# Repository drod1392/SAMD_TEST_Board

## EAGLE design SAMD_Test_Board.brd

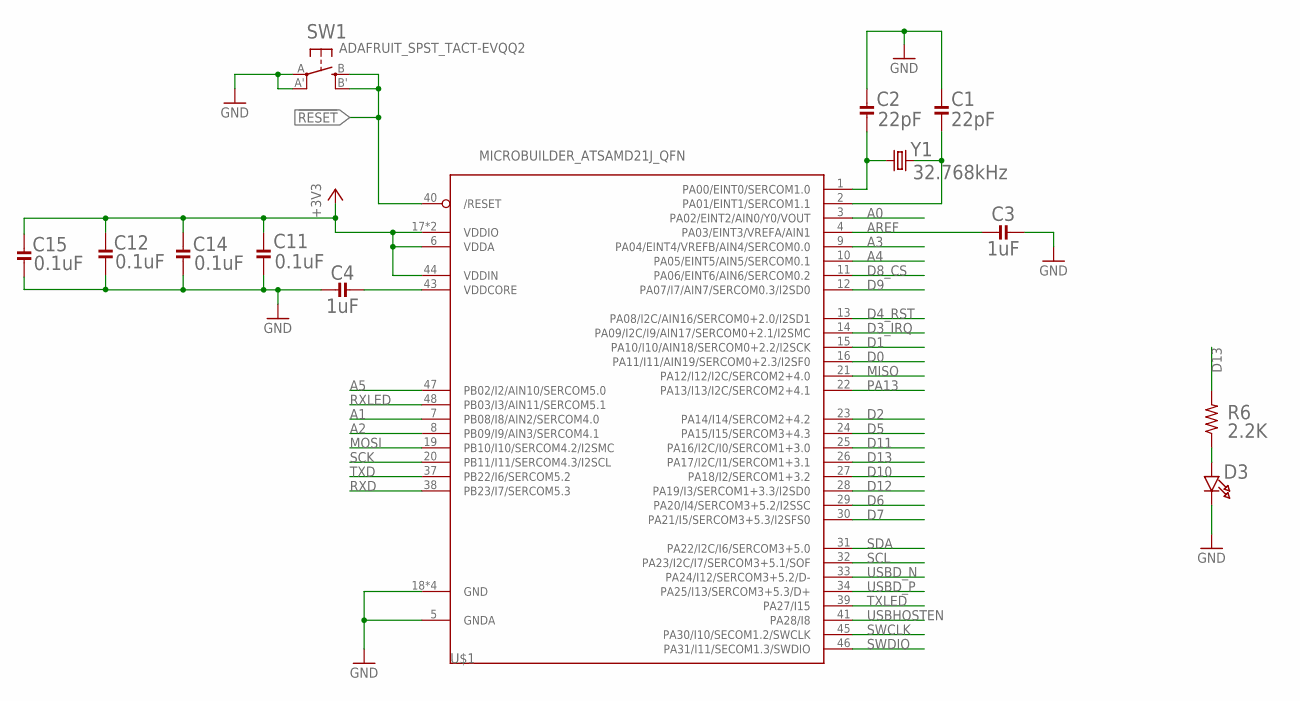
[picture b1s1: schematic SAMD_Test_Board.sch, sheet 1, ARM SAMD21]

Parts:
C1, C2: 22pF; MICROBUILDER__0805
C3, C4: 1uF; MICROBUILDER__0805
C11, C12, C14, C15: 0.1uF; MICROBUILDER__0805
D3: MICROBUILDER_LED0603; MICROBUILDER_CHIPLED_0603
R6: 2.2K; R0805
SW1: ADAFRUIT_SPST_TACT-EVQQ2; ADAFRUIT_EVQ-Q2
U$1: MICROBUILDER_ATSAMD21J_QFN; MICROBUILDER_TQFN48_7MM
Y1: 32.768kHz; CRYSTAL-SMD-3.2X1.5MM

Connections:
!RESET: SW1.B (S), SW1.B' (S1), U$1.40 (/RESET)
+3V3: C11.2, C12.2, C14.2, C15.2, U$1.6 (VDDA), U$1.17 (VDDIO), U$1.36 (VDDIO), U$1.44 (VDDIN); also elsewhere on the board
A0: U$1.3 (PA02/EINT2/AIN0/Y0/VOUT)
A1: U$1.7 (PB08/I8/AIN2/SERCOM4.0)
A2: U$1.8 (PB09/I9/AIN3/SERCOM4.1)
A3: U$1.9 (PA04/EINT4/VREFB/AIN4/SERCOM0.0)
A4: U$1.10 (PA05/EINT5/AIN5/SERCOM0.1)
A5: U$1.47 (PB02/I2/AIN10/SERCOM5.0)
AREF: C3.2, U$1.4 (PA03/EINT3/VREFA/AIN1)
D0: U$1.16 (PA11/I11/AIN19/SERCOM0+2.3/I2SF0); also elsewhere on the board
D1: U$1.15 (PA10/I10/AIN18/SERCOM0+2.2/I2SCK)
D2: U$1.23 (PA14/I14/SERCOM2+4.2)
D3_IRQ: U$1.14 (PA09/I2C/I9/AIN17/SERCOM0+2.1/I2SMC); also elsewhere on the board
D4_RST: U$1.13 (PA08/I2C/AIN16/SERCOM0+2.0/I2SD1); also elsewhere on the board
D5: U$1.24 (PA15/I15/SERCOM3+4.3)
D6: U$1.29 (PA20/I4/SERCOM3+5.2/I2SSC)
D7: U$1.30 (PA21/I5/SERCOM3+5.3/I2SFS0)
D8_CS: U$1.11 (PA06/EINT6/AIN6/SERCOM0.2); also elsewhere on the board
D9: U$1.12 (PA07/I7/AIN7/SERCOM0.3/I2SD0); also elsewhere on the board
D10: U$1.27 (PA18/I2/SERCOM1+3.2)
D11: U$1.25 (PA16/I2C/I0/SERCOM1+3.0); also elsewhere on the board
D12: U$1.28 (PA19/I3/SERCOM1+3.3/I2SD0)
D13: R6.2, U$1.26 (PA17/I2C/I1/SERCOM1+3.1)
GND: C1.2, C2.2, C3.1, C4.2, C11.1, C12.1, C14.1, C15.1, D3.C, SW1.A, SW1.A' (P1), U$1.5 (GNDA), U$1.18 (GND), U$1.35 (GND), U$1.42 (GND), U$1.THERMAL (GND); also elsewhere on the board
MISO: U$1.21 (PA12/I12/I2C/SERCOM2+4.0); also elsewhere on the board
MOSI: U$1.19 (PB10/I10/SERCOM4.2/I2SMC); also elsewhere on the board
unnamed: C2.1, U$1.1 (PA00/EINT0/SERCOM1.0), Y1.P$1 (1)
unnamed: C1.1, U$1.2 (PA01/EINT1/SERCOM1.1), Y1.P$2 (2)
unnamed: C4.1, U$1.43 (VDDCORE)
unnamed: D3.A, R6.1
PA13: U$1.22 (PA13/I13/I2C/SERCOM2+4.1)
RXD: U$1.38 (PB23/I7/SERCOM5.3)
RXLED: U$1.48 (PB03/I3/AIN11/SERCOM5.1)
SCK: U$1.20 (PB11/I11/SERCOM4.3/I2SCL); also elsewhere on the board
SCL: U$1.32 (PA23/I2C/I7/SERCOM3+5.1/SOF); also elsewhere on the board
SDA: U$1.31 (PA22/I2C/I6/SERCOM3+5.0); also elsewhere on the board
SWCLK: U$1.45 (PA30/I10/SECOM1.2/SWCLK); also elsewhere on the board
SWDIO: U$1.46 (PA31/I11/SECOM1.3/SWDIO); also elsewhere on the board
TXD: U$1.37 (PB22/I6/SERCOM5.2)
TXLED: U$1.39 (PA27/I15)
USBD_N: U$1.33 (PA24/I12/SERCOM3+5.2/D-); also elsewhere on the board
USBD_P: U$1.34 (PA25/I13/SERCOM3+5.3/D+); also elsewhere on the board
USBHOSTEN: U$1.41 (PA28/I8)

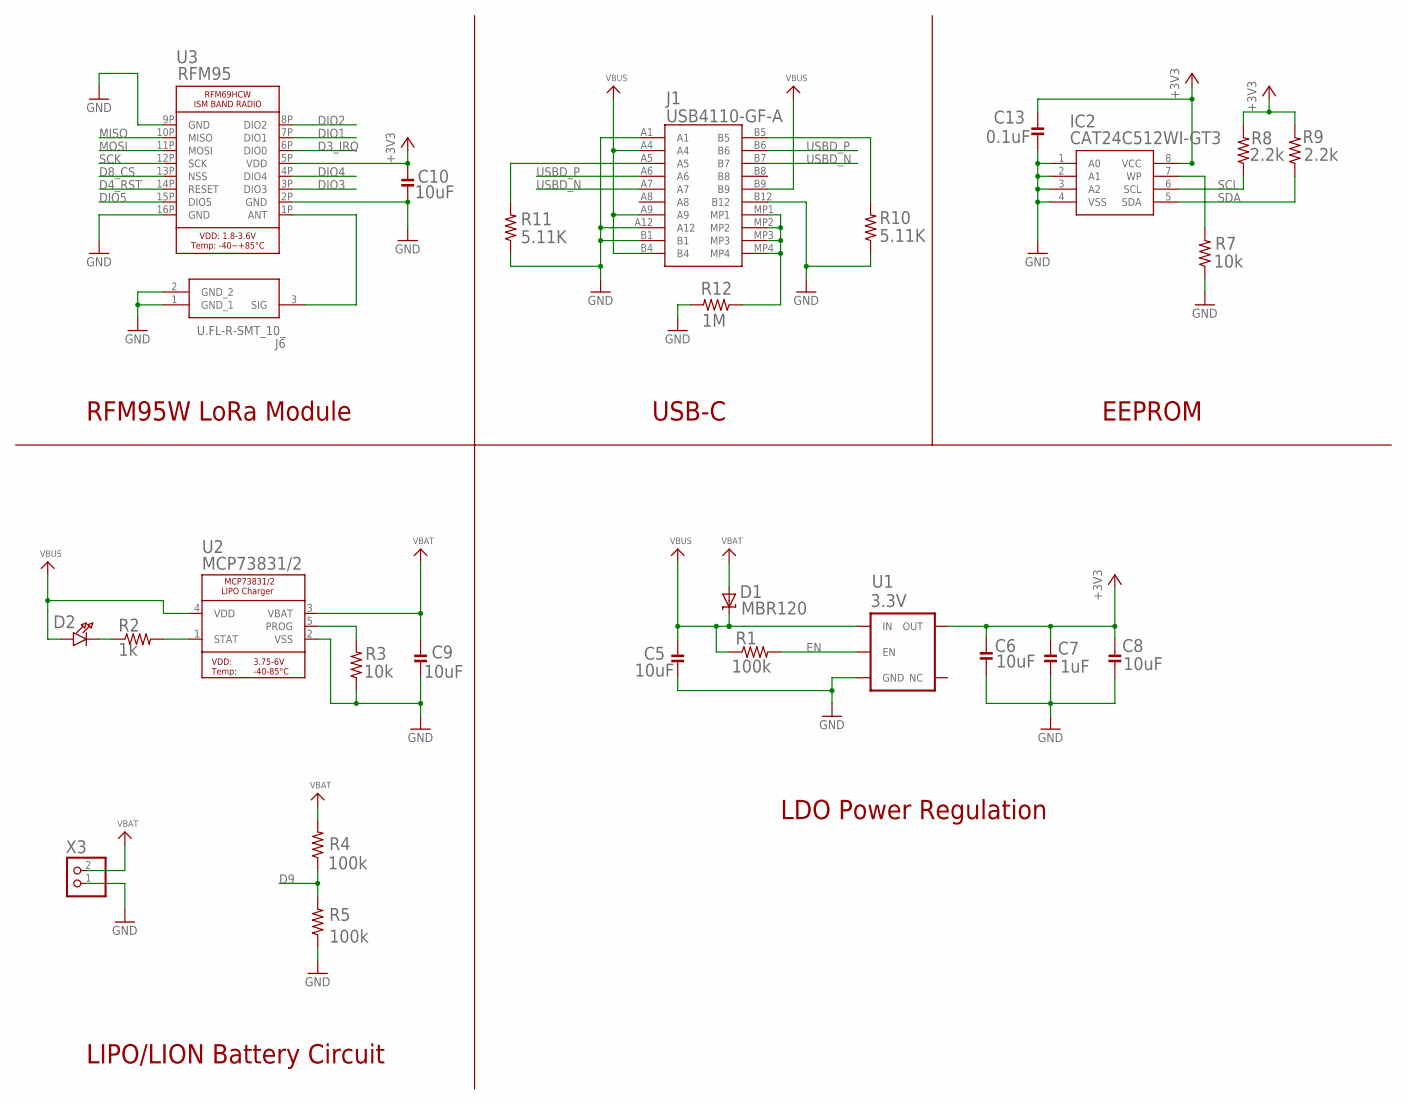
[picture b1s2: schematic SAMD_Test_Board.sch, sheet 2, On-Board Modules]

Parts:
C5, C6, C8, C9, C10: 10uF; MICROBUILDER__0805
C7: 1uF; MICROBUILDER__0805
C13: 0.1uF; MICROBUILDER__0805
D1: MBR120; MICROBUILDER_SOD-123
D2: MICROBUILDER_LED0603; MICROBUILDER_CHIPLED_0603
IC2: CAT24C512WI-GT3; SOIC127P600X175-8N
J1: USB4110-GF-A; USB4110GFA
J6: U.FL-R-SMT_10_; UFLRSMT10
R1, R4, R5: 100k; R0805
R2: 1k; R0805
R3, R7: 10k; R0805
R8: 2.2k; R0805; MOUSER CR0805-JW-202ELF
R9: 2.2k; R0805
R10, R11: 5.11K; R0805
R12: 1M; R0805
U1: 3.3V; SOT23-5
U2: MCP73831/2; MICROBUILDER_SOT23-5
U3: RFM95; MICROBUILDER_RFMHCW_SMT
X3: MICROBUILDER_CON_JST_PH_2PIN; MICROBUILDER_JSTPH2

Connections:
+3V3: C6.2, C7.2, C8.2, C10.2, C13.2, IC2.8 (VCC), R8.2, R9.2, U1.5 (OUT), U3.5P (VDD); also elsewhere on the board
D3_IRQ: U3.6P (DIO0); also elsewhere on the board
D4_RST: U3.14P (RESET); also elsewhere on the board
D8_CS: U3.13P (NSS); also elsewhere on the board
D9: R4.1, R5.2; also elsewhere on the board
DIO1: U3.7P (DIO1)
DIO2: U3.8P (DIO2)
DIO3: U3.3P (DIO3)
DIO4: U3.4P (DIO4)
DIO5: U3.15P (DIO5)
EN: R1.2, U1.3 (EN); also elsewhere on the board
GND: C5.1, C6.1, C7.1, C8.1, C9.1, C10.1, C13.1, IC2.1 (A0), IC2.2 (A1), IC2.3 (A2), IC2.4 (VSS), J1.A1, J1.A12, J1.B1, J1.B12, J6.1 (GND_1), J6.2 (GND_2), R3.1, R5.1, R7.1, R10.1, R11.1, R12.2, U1.2 (GND), U2.2 (VSS), U3.2P (GND), U3.9P (GND), U3.16P (GND), X3.1; also elsewhere on the board
MISO: U3.10P (MISO); also elsewhere on the board
MOSI: U3.11P (MOSI); also elsewhere on the board
unnamed: IC2.7 (WP), R7.2
unnamed: J1.A5, R11.2
unnamed: D2.C, R2.1
unnamed: R2.2, U2.1 (STAT)
unnamed: R3.2, U2.5 (PROG)
unnamed: J1.B5, R10.2
unnamed: J1.MP1, J1.MP2, J1.MP3, J1.MP4, R12.1
unnamed: J6.3 (SIG), U3.1P (ANT)
SCK: U3.12P (SCK); also elsewhere on the board
SCL: IC2.6 (SCL), R8.1; also elsewhere on the board
SDA: IC2.5 (SDA), R9.1; also elsewhere on the board
USBD_N: J1.A7, J1.B7; also elsewhere on the board
USBD_P: J1.A6, J1.B6; also elsewhere on the board
VBAT: C9.2, D1.A, R4.2, U2.3 (VBAT), X3.2
VBUS: C5.2, D1.C, D2.A, J1.A4, J1.A9, J1.B4, J1.B9, R1.1, U1.1 (IN), U2.4 (VDD)

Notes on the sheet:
LIPO/LION Battery Circuit
RFM95W LoRa Module
USB-C
EEPROM
LDO Power Regulation

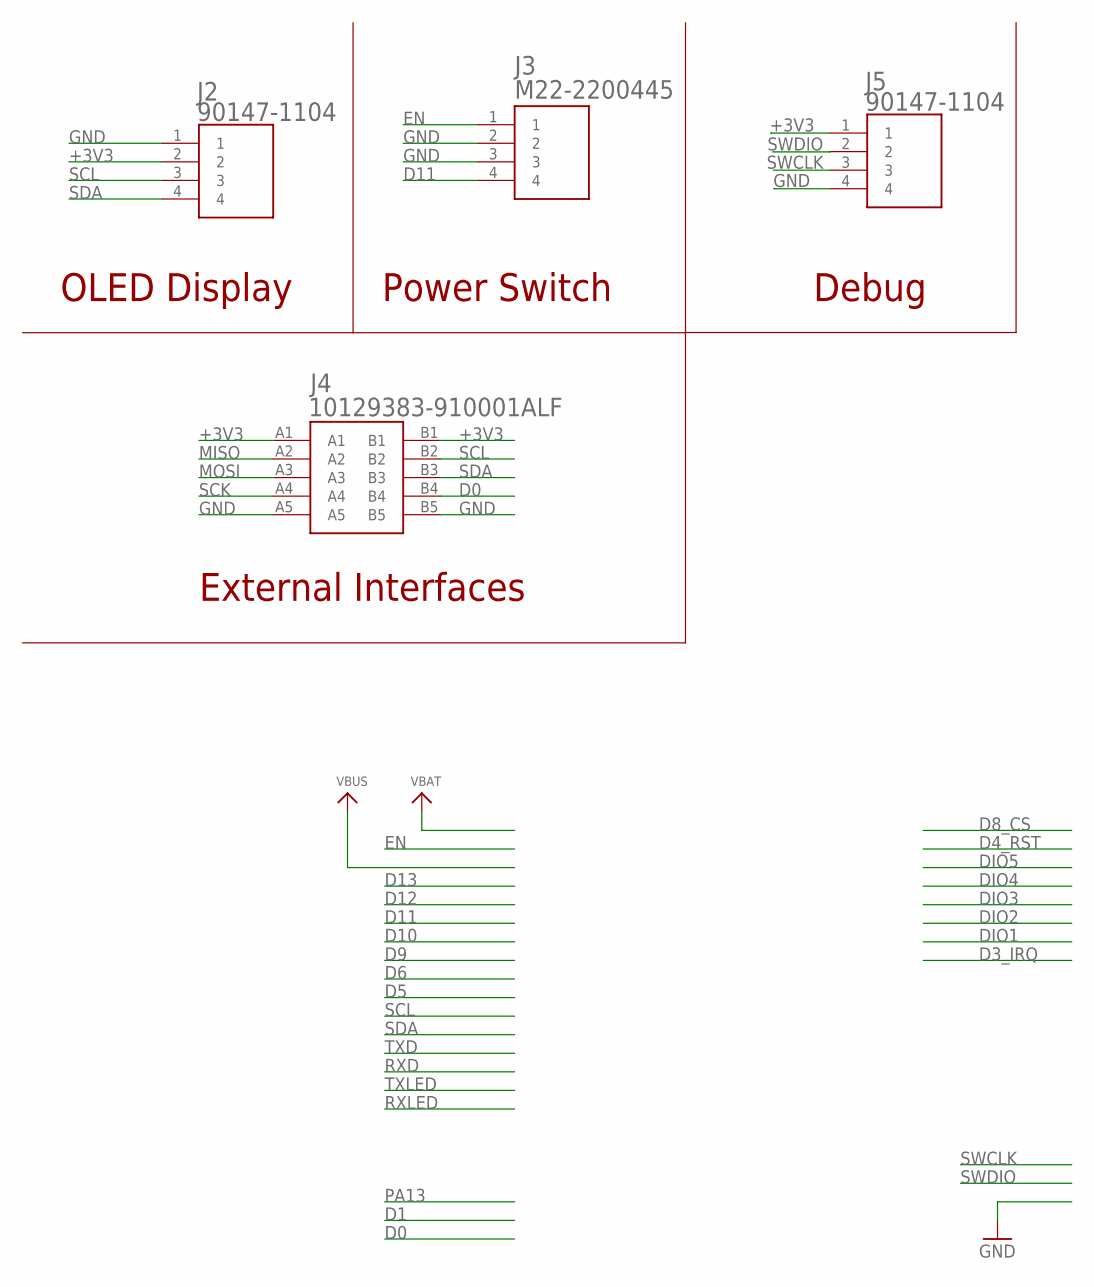
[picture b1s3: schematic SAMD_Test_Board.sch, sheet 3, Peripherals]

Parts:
J2, J5: 90147-1104; RHDR4W70P0X254_1X4_1016X244X87
J3: M22-2200445; SHDR4W50P0X200_1X4_1000X470X63
J4: 10129383-910001ALF; 10129383910001ALF

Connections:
+3V3: J2.2, J4.A1, J4.B1, J5.1; also elsewhere on the board
D0: J4.B4; also elsewhere on the board
D11: J3.4; also elsewhere on the board
EN: J3.1; also elsewhere on the board
GND: J2.1, J3.2, J3.3, J4.A5, J4.B5, J5.4; also elsewhere on the board
MISO: J4.A2; also elsewhere on the board
MOSI: J4.A3; also elsewhere on the board
SCK: J4.A4; also elsewhere on the board
SCL: J2.3, J4.B2; also elsewhere on the board
SDA: J2.4, J4.B3; also elsewhere on the board
SWCLK: J5.3; also elsewhere on the board
SWDIO: J5.2; also elsewhere on the board

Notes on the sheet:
OLED Display
Power Switch
Debug
External Interfaces

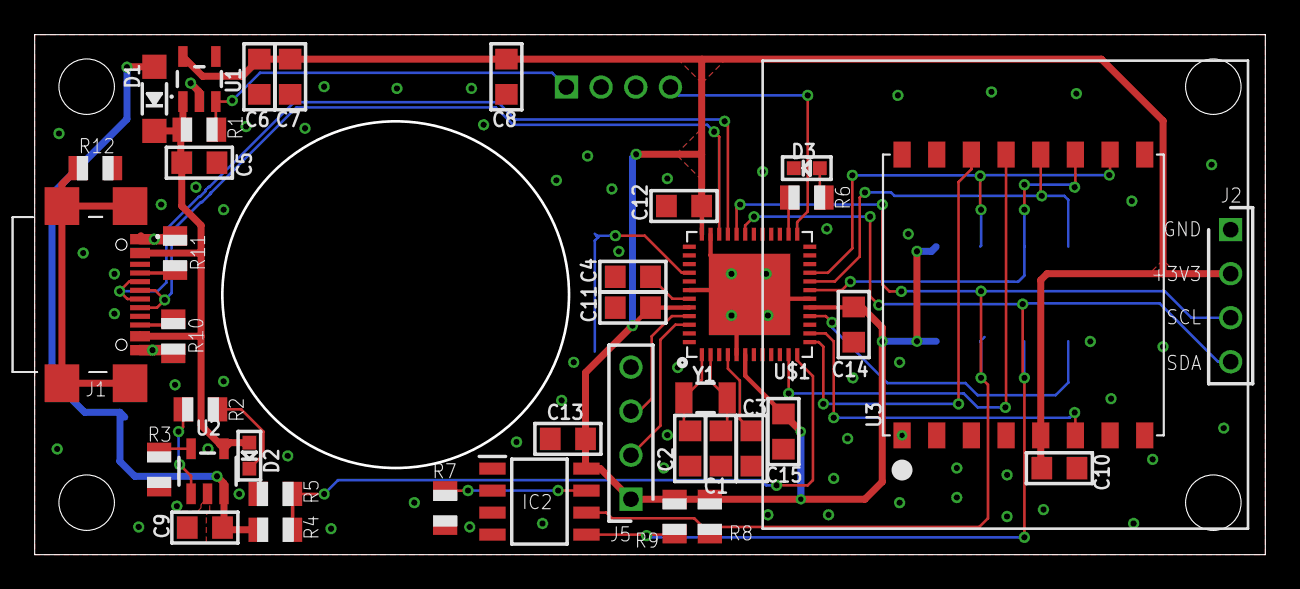
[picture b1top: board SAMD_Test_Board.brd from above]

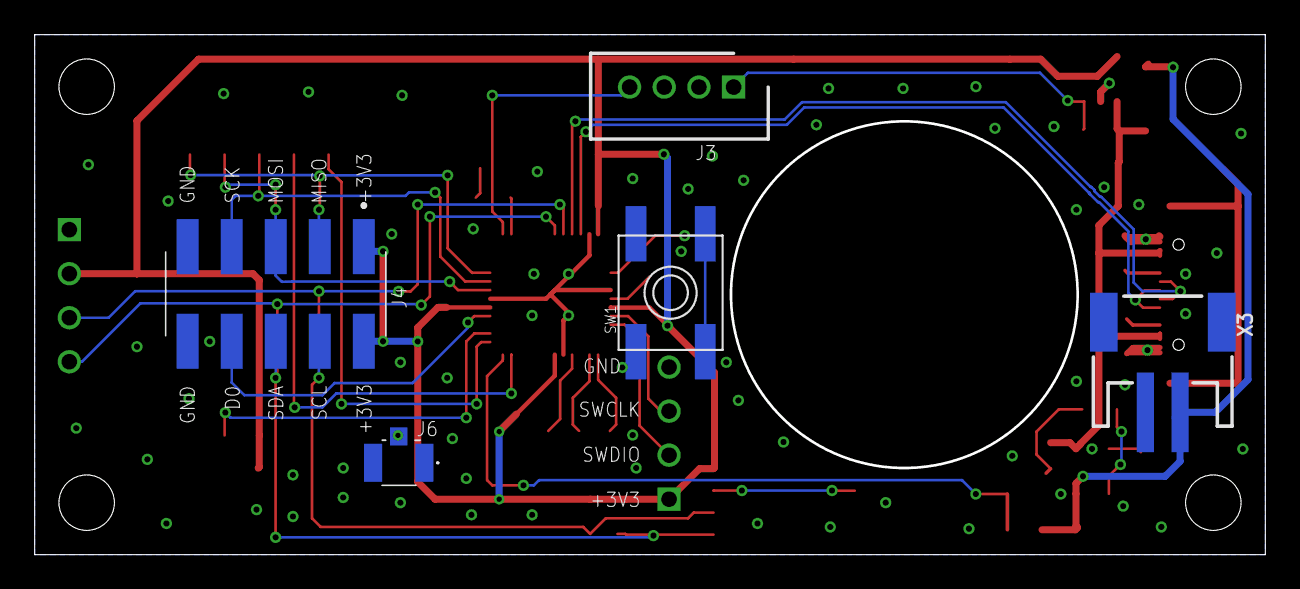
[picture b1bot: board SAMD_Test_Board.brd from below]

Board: 2 copper layers, 70.8 x 29.8 mm, 44 parts (5 on the bottom side), 35 nets.

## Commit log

2022-01-31 added .gitignore
2022-01-31 edit .gitignore
2022-02-01 updated .gitignore
2022-02-01 Initial Board Commit

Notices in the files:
parts and their libraries:
SparkFun-Clocks: Licensing: Creative Commons ShareAlike 4.0 International - https://creativecommons.org/licenses/by-sa/4.0
